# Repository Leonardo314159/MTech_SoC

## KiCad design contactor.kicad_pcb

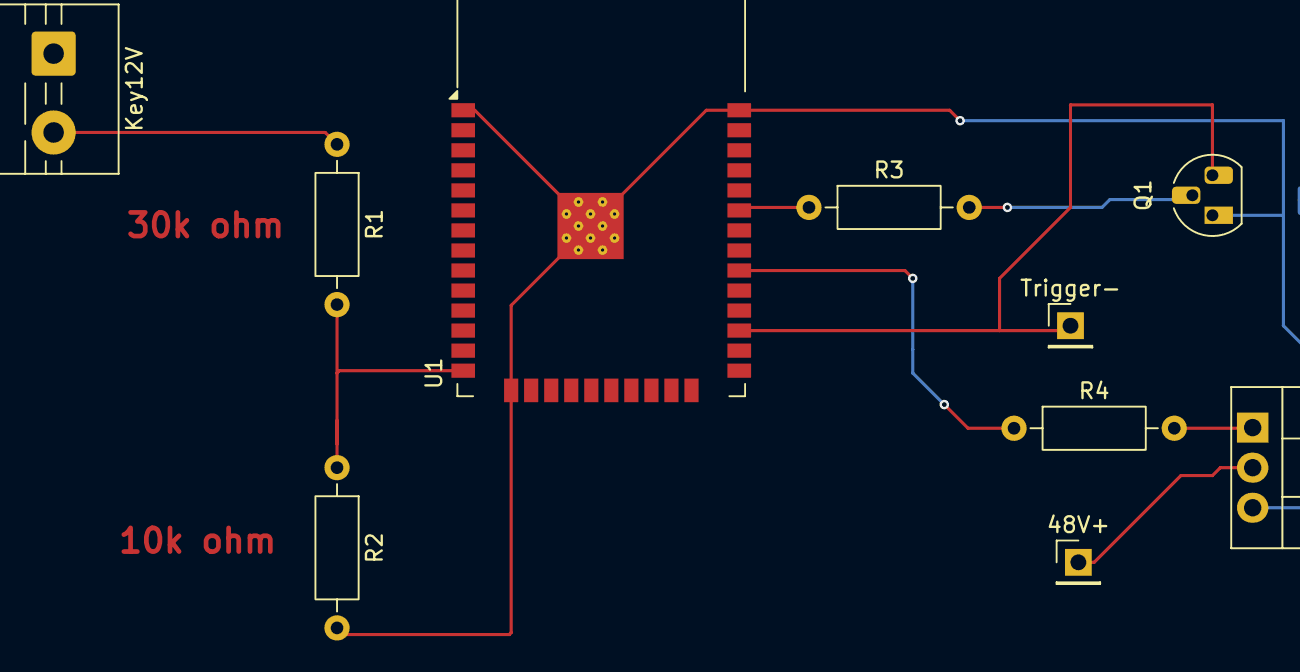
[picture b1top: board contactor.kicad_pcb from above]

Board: 2 copper layers, 10 parts (0 on the bottom side), 5 nets.

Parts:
48V+: 0; PinHeader_1x01_P2.54mm_Vertical
Key12V: 12v; TerminalBlock_MaiXu_MX126-5.0-02P_1x02_P5.00mm
Q1: BC337; TO-92_HandSolder
Q2: IRLZ44N; TO-220-3_Vertical
R1: 30000; R_Axial_DIN0207_L6.3mm_D2.5mm_P10.16mm_Horizontal
R2: 10000; R_Axial_DIN0207_L6.3mm_D2.5mm_P10.16mm_Horizontal
R3, R4: 1000; R_Axial_DIN0207_L6.3mm_D2.5mm_P10.16mm_Horizontal
Trigger-: 0; PinHeader_1x01_P2.54mm_Vertical
U1: ESP32-WROOM-32

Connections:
12: Q2.1, R4.2
48+: 48V+.1, Q2.2
unnamed: Q1.1, Q2.3, R2.2, U1.1 (GND), U1.15 (GND), U1.38 (GND), U1.39 (GND)
R1+: Key12V.2, R1.1
R3+: Q1.2, R3.2

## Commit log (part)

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2026-06-30 Basic I2C Communication
2026-06-30 Tested & Working. small tweaks
2026-06-30 Schematic is finished. PCB Could use some work
2026-06-30 Figured out how to do headers. all that is left is SoC
